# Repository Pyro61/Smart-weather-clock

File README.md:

# Smart Weather Clock

A real-time clock system with configurable alarms and integrated weather sensing, built on the STM32G474RE microcontroller. Combines internal and external sensors with a simple user interface and Bluetooth-based data expansion.

---

## Project Goals

This project was developed as a learning exercise with the following goals:

- Practice **bare-metal programming** using direct register access on STM32 microcontrollers
- Design the system so that most tasks are handled via **interrupts**, not the main loop — to reduce power consumption
- Learn to build embedded projects using a **build system (CMake)** instead of IDE-generated Makefiles
- Improve fluency with **Git version control** and good repository structure
- Gain experience in **PCB design**

---

## Features

- Real-Time Clock (RTC) with support for a single configurable alarm
- Weather sensing:
  - **Internal sensors**:
    - Temperature & Pressure: LPS25HB (I2C)
    - Humidity: SHT20 (I2C)
  - **External sensors** (via Bluetooth HC-05):
    - Temperature, Pressure, Humidity, Rain Detection
- Periodic weather update every 10 seconds
- Automatic low-power sleep mode:
  - System enters sleep after completing all tasks in the main loop
  - Wakes up on interrupts (e.g., timer or button press)
- User-selectable weather data source (internal or external)
- Alarm notifications:
  - Display alert
  - External buzzer module with built-in sound generator (controlled via GPIO)
- LCD display: 20x4 alphanumeric, driven by HD44780 controller
- User interface:
  - Push-buttons for navigation and settings
  - Potentiometer for adjusting LCD contrast

---

## Hardware Overview

- **Microcontroller**: STM32G474RE
- **Display**: 20x4 LCD with HD44780 controller (parallel interface)
- **Internal Sensors**:
  - LPS25HB (temperature and pressure, I2C)
  - SHT20 (humidity, I2C)
- **External Sensor Module**:
  - Communicates over UART via HC-05 Bluetooth
  - Sends temperature, pressure, humidity, and rain data
- **Buzzer Module**:
  - External buzzer with internal sound generator
  - Controlled via logic-level GPIO
- **User Inputs**:
  - Buttons:
    - OK / Mode
    - Up
    - Down
    - Left
    - Right
  - Potentiometer for LCD contrast

---

## How It Works

1. On startup, the system initializes:
   - MCU embedded peripherals (RTC, UART, GPIO, RTC etc.)
   - Internal sensors
   - LCD

3. Default behavior after power reset:
   - RTC time = 00:00:00
   - Alarm = disabled
   - Weather readings from internal sensors

4. System behavior:
   - Sensor readings are updated every 10 seconds
   - Every second current time and sensor readings are displayed on the screen
   - After processing all events and interrupts, the system enters low-power mode until the next interrupt

5. The default screen shows:
   - Current time
   - Alarm status
   - Sensor data (internal by default)

6. Pressing **OK / Mode** opens a menu with 4 options. The currently selected option is marked with `>` e.g:
```
   > 1. weather indoor  
     2. weather outdoor  
     3. set time  
     4. set alarm
```

7. Navigation:
   - **Up / Down** to move through options
   - **OK / Mode** to select
   - In `Set Time` and `Set Alarm`:
     - **Left / Right** to move between HH:MM:SS
     - **Up / Down** to adjust values

8. Alarm behavior:
   - When alarm is enabled and the current time matches the alarm:
     - "ALARM" screen is displayed
     - Buzzer is activated via GPIO

---

## User Interface

After system startup and peripheral initialization, the main screen displays:
- Current time (reset to 00:00:00 after power-off — no backup battery for RTC)
- Alarm status (disabled after power reset)
- Live weather readings from internal sensors

### Navigation Summary

- **OK / Mode**: Enter menu / confirm selection
- **Up / Down**: Scroll through menu or increment/decrement values
- **Left / Right**: Switch between hours, minutes, seconds

---

## Getting Started

1. Clone this repository.
2. Build the project using CMake
3. Flash the firmware to STM32G474RE (e.g., Nucleo board).
4. Connect all sensors and peripherals according to the labeled connectors on the [custom PCB](pcb/main_board/main_board_pcb.png) or according to [wiring diagram](pcb/main_board/main_board_schematic.png).

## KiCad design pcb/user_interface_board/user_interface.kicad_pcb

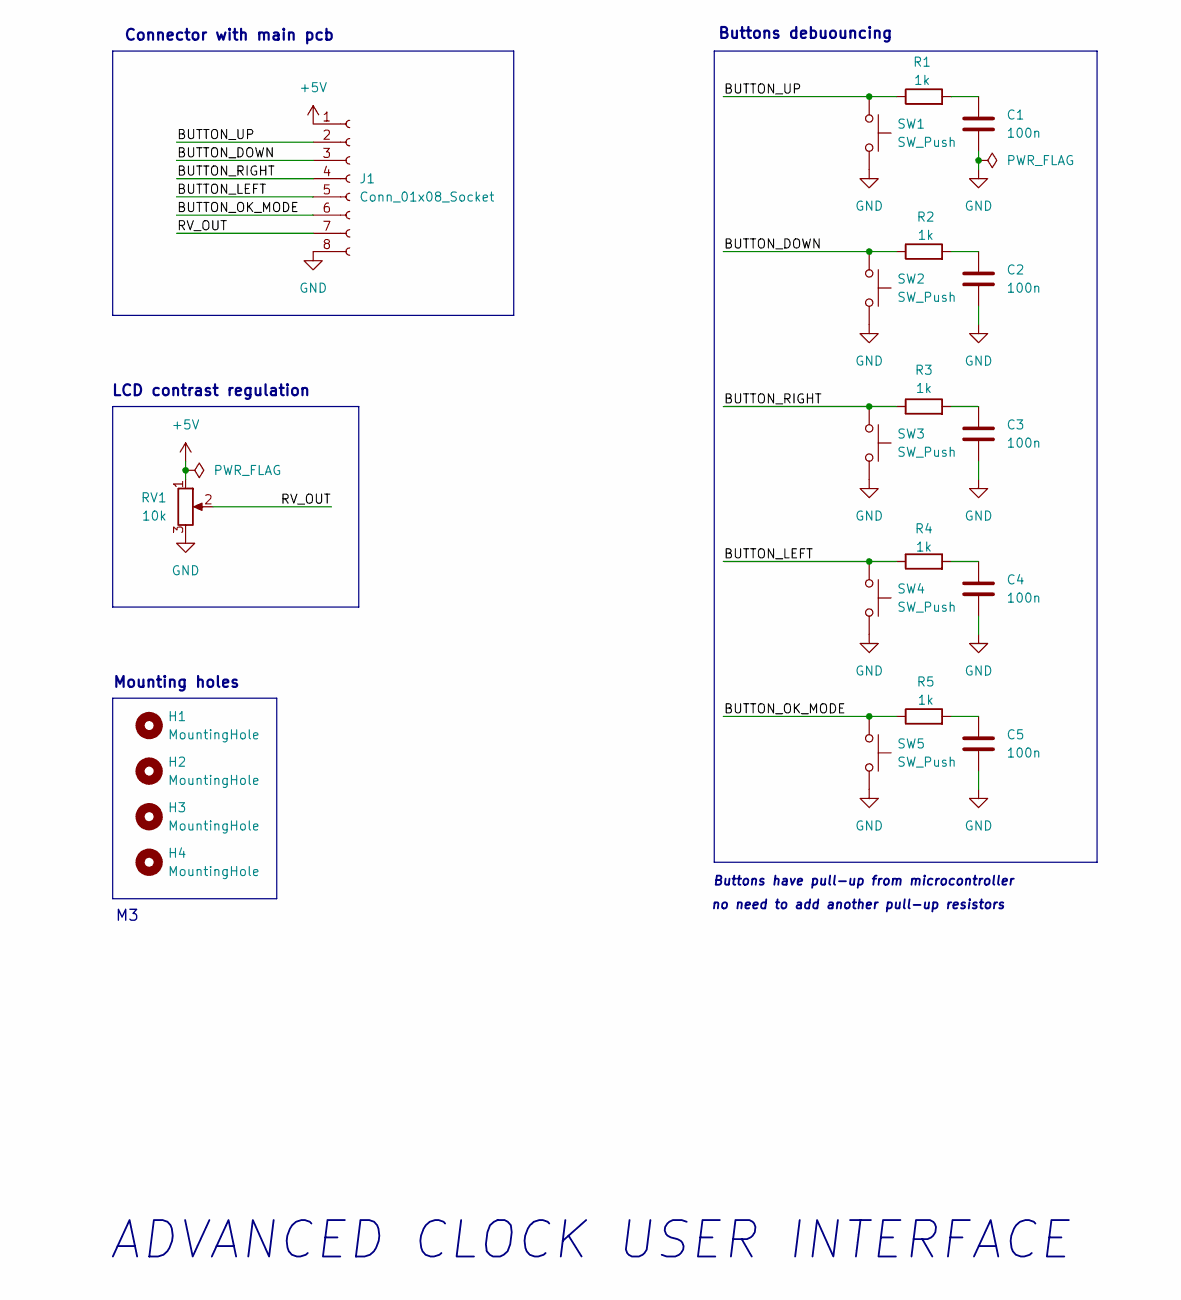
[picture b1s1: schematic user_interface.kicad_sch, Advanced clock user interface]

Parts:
C1, C2, C3, C4, C5: 100n; C_0402_1005Metric
H1, H2, H3, H4: MountingHole; MountingHole_3.2mm_M3
J1: Conn_01x08_Socket; PinSocket_1x08_P2.54mm_Vertical
R1, R2, R3, R4, R5: 1k; R_0402_1005Metric
RV1: 10k; Potentiometer_Bourns_3339P_Vertical_HandSoldering
SW1, SW2, SW3, SW4, SW5: SW_Push; SW_PUSH_6mm_H7.3mm

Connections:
+5V: J1.1, RV1.1
/BUTTON_DOWN: J1.3, R2.1, SW2.1
/BUTTON_LEFT: J1.5, R4.1, SW4.1
/BUTTON_OK_MODE: J1.6, R5.1, SW5.1
/BUTTON_RIGHT: J1.4, R3.1, SW3.1
/BUTTON_UP: J1.2, R1.1, SW1.1
/RV_OUT: J1.7, RV1.2
GND: C1.2, C2.2, C3.2, C4.2, C5.2, J1.8, RV1.3, SW1.2, SW2.2, SW3.2, SW4.2, SW5.2
unnamed: C1.1, R1.2
unnamed: C2.1, R2.2
unnamed: C3.1, R3.2
unnamed: C4.1, R4.2
unnamed: C5.1, R5.2

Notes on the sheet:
Buttons have pull-up from microcontroller
Mounting holes
LCD contrast regulation
Buttons debuouncing
no need to add another pull-up resistors
Connector with main pcb
ADVANCED CLOCK USER INTERFACE

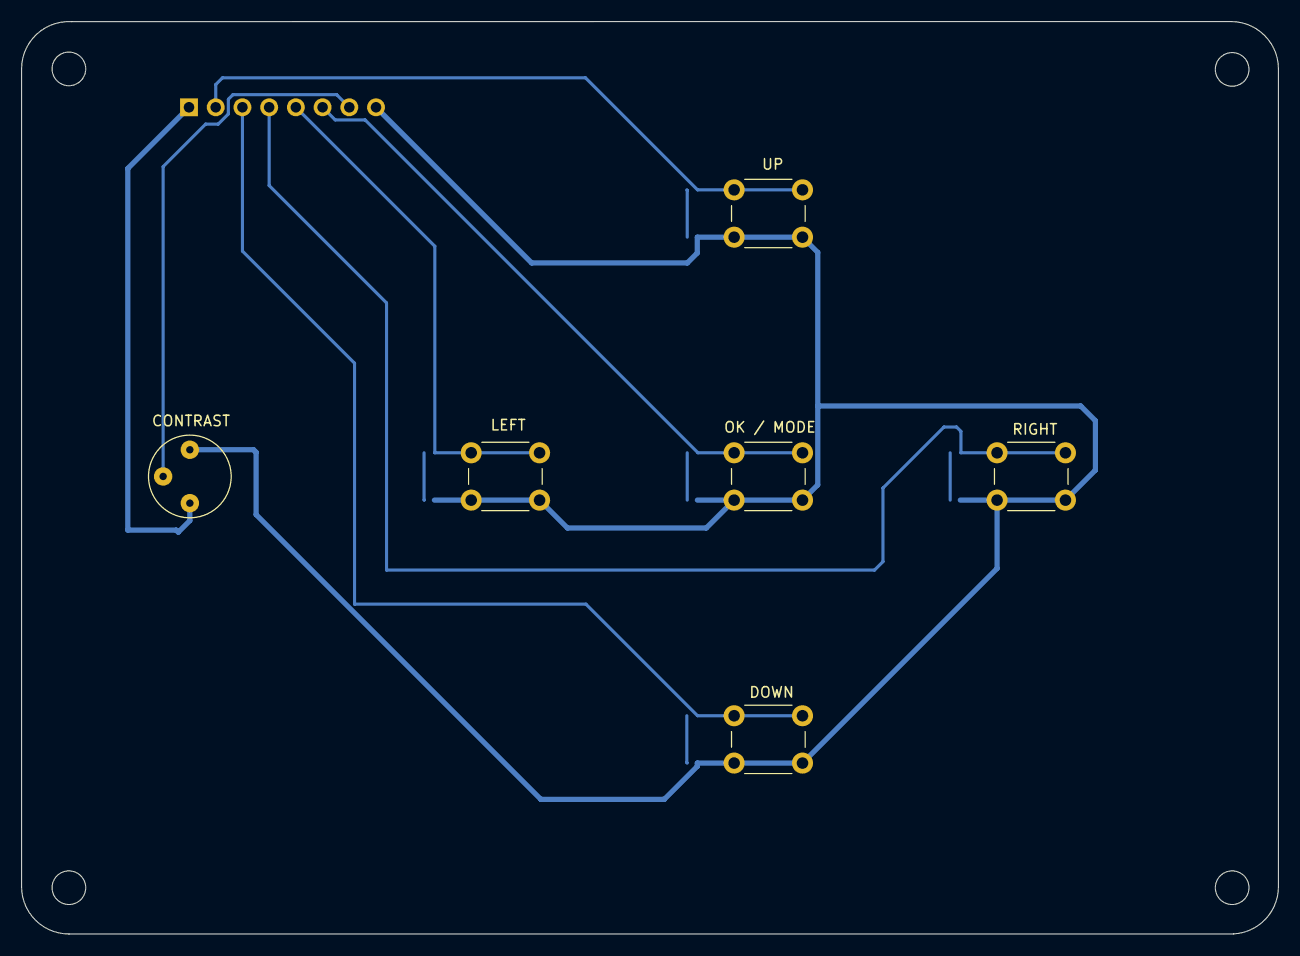
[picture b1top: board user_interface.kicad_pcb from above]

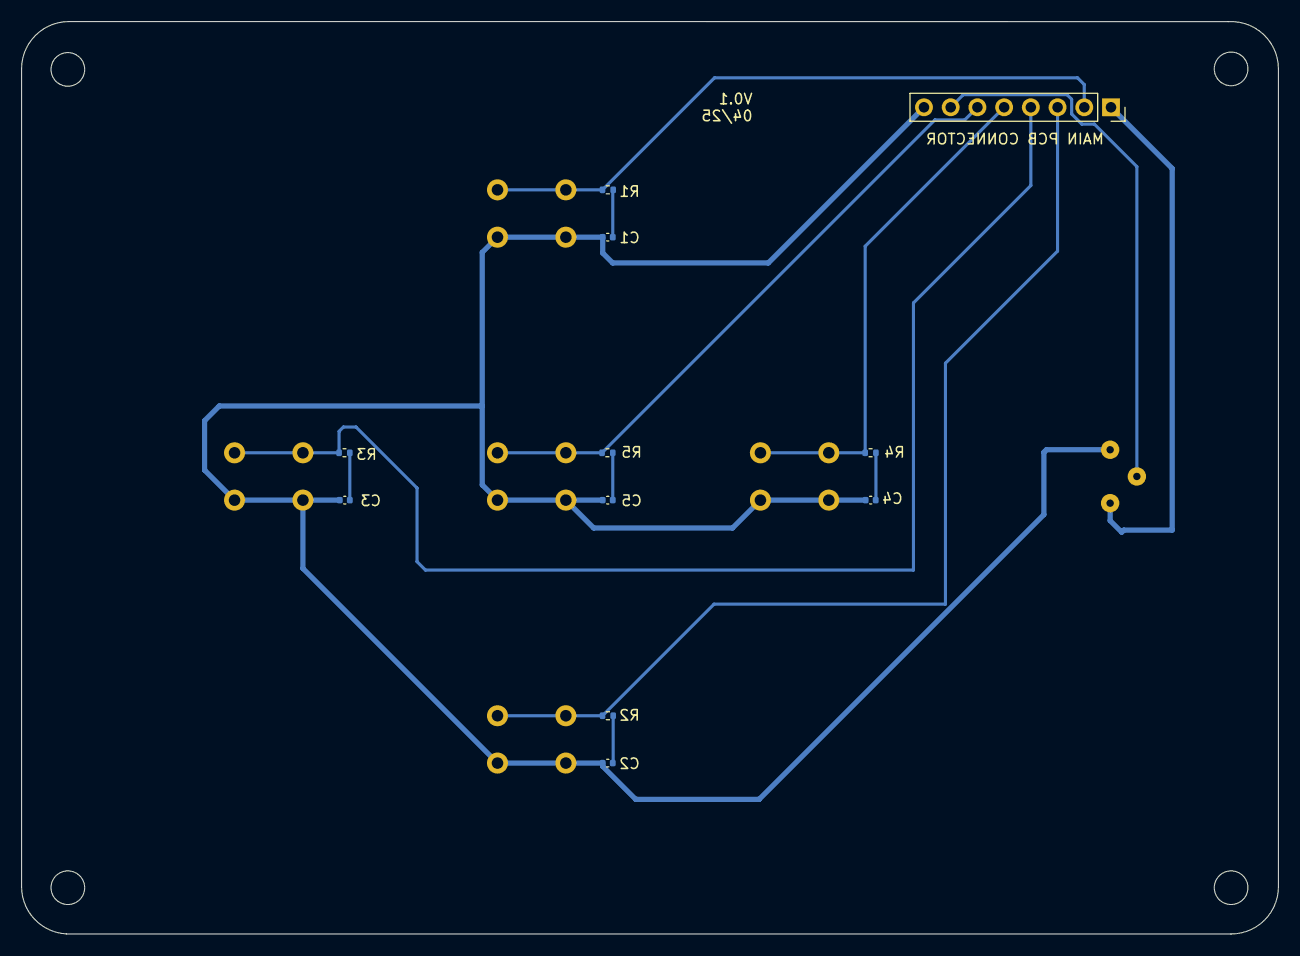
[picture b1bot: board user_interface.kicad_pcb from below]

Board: 2 copper layers, 119.5 x 86.8 mm, 21 parts (11 on the bottom side), 13 nets.

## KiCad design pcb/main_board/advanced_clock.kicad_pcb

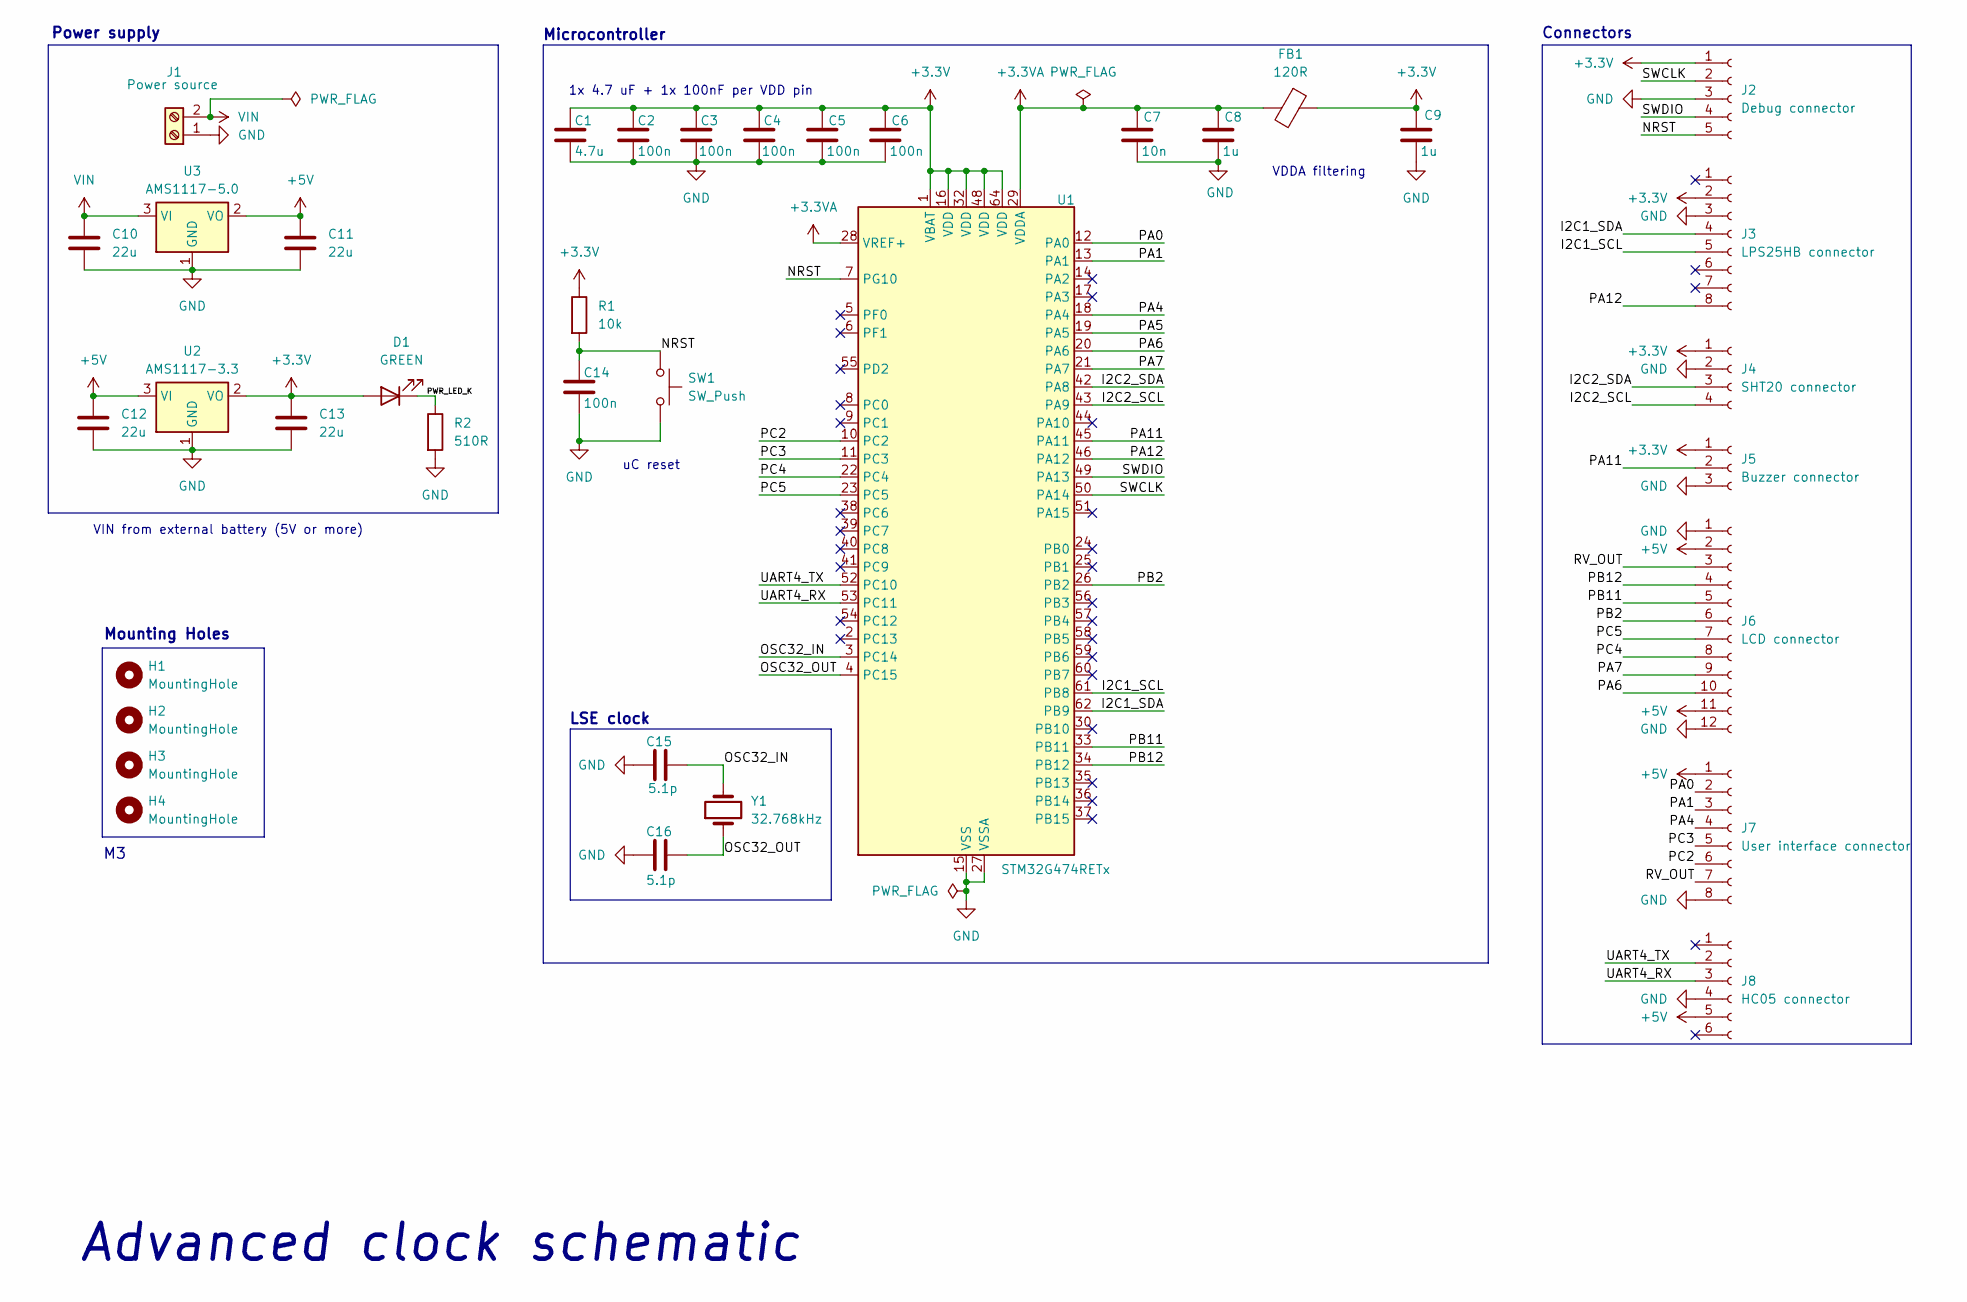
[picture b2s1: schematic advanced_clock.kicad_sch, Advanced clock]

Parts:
C1: 4.7u; C_0504_1310Metric
C2, C3, C4, C5, C6, C14: 100n; C_0402_1005Metric
C7: 10n; C_0402_1005Metric
C8, C9: 1u; C_0402_1005Metric
C10, C11, C12, C13: 22u; C_0805_2012Metric
C15, C16: 5.1p; C_0402_1005Metric
D1: GREEN; LED_0402_1005Metric
FB1: 120R; L_0603_1608Metric
H1, H2, H3, H4: MountingHole; MountingHole_3.2mm_M3
J1: Power source; TerminalBlock_Phoenix_MKDS-1,5-2-5.08_1x02_P5.08mm_Horizont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
J2: Debug connector; PinSocket_1x05_P2.54mm_Vertical
J3: LPS25HB connector; PinSocket_1x08_P2.54mm_Vertical
J4: SHT20 connector; PinSocket_1x04_P2.54mm_Vertical
J5: Buzzer connector; PinSocket_1x03_P2.54mm_Vertical
J6: LCD connector; PinSocket_1x12_P2.54mm_Vertical
J7: User interface connector; PinSocket_1x08_P2.54mm_Vertical
J8: HC05 connector; PinSocket_1x06_P2.54mm_Vertical
R1: 10k; R_0402_1005Metric
R2: 510R; R_0402_1005Metric
SW1: SW_Push; SW_PUSH_6mm_H7.3mm
U1: STM32G474RETx; LQFP-64_10x10mm_P0.5mm
U2: AMS1117-3.3; SOT-223-3_TabPin2
U3: AMS1117-5.0; SOT-223-3_TabPin2
Y1: 32.768kHz; Crystal_SMD_2012-2Pin_2.0x1.2mm

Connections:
+3.3V: C1.1, C2.1, C3.1, C4.1, C5.1, C6.1, C9.1, C13.1, D1.2 (A), FB1.1, J2.1, J3.2, J4.1, J5.1, R1.1, U1.1 (VBAT), U1.16 (VDD), U1.32 (VDD), U1.48 (VDD), U1.64 (VDD), U2.2 (VO)
+3.3VA: C7.1, C8.1, FB1.2, U1.28 (VREF+), U1.29 (VDDA)
+5V: C11.1, C12.1, J6.2, J6.11, J7.1, J8.5, U2.3 (VI), U3.2 (VO)
/I2C1_SCL: J3.5, U1.61 (PB8)
/I2C1_SDA: J3.4, U1.62 (PB9)
/I2C2_SCL: J4.4, U1.43 (PA9)
/I2C2_SDA: J4.3, U1.42 (PA8)
/NRST: C14.1, J2.5, R1.2, SW1.1, U1.7 (PG10)
/OSC32_IN: C15.2, U1.3 (PC14), Y1.2
/OSC32_OUT: C16.2, U1.4 (PC15), Y1.1
/PA0: J7.2, U1.12 (PA0)
/PA1: J7.3, U1.13 (PA1)
/PA4: J7.4, U1.18 (PA4)
/PA5: U1.19 (PA5)
/PA6: J6.10, U1.20 (PA6)
/PA7: J6.9, U1.21 (PA7)
/PA11: J5.2, U1.45 (PA11)
/PA12: J3.8, U1.46 (PA12)
/PB2: J6.6, U1.26 (PB2)
/PB11: J6.5, U1.33 (PB11)
/PB12: J6.4, U1.34 (PB12)
/PC2: J7.6, U1.10 (PC2)
/PC3: J7.5, U1.11 (PC3)
/PC4: J6.8, U1.22 (PC4)
/PC5: J6.7, U1.23 (PC5)
/PWR_LED_K: D1.1 (K), R2.1
/RV_OUT: J6.3, J7.7
/SWCLK: J2.2, U1.50 (PA14)
/SWDIO: J2.4, U1.49 (PA13)
/UART4_RX: J8.3, U1.53 (PC11)
/UART4_TX: J8.2, U1.52 (PC10)
GND: C1.2, C2.2, C3.2, C4.2, C5.2, C6.2, C7.2, C8.2, C9.2, C10.2, C11.2, C12.2, C13.2, C14.2, C15.1, C16.1, J1.1, J2.3, J3.3, J4.2, J5.3, J6.1, J6.12, J7.8, J8.4, R2.2, SW1.2, U1.15 (VSS), U1.27 (VSSA), U1.31 (VSS), U1.47 (VSS), U1.63 (VSS), U2.1 (GND), U3.1 (GND)
VIN: C10.1, J1.2, U3.3 (VI)

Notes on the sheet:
1x 4.7 uF + 1x 100nF per VDD pin
Mounting Holes
uC reset
Power supply
VDDA filtering
VIN from external battery (5V or more)
LSE clock
Connectors
Microcontroller
Advanced clock schematic

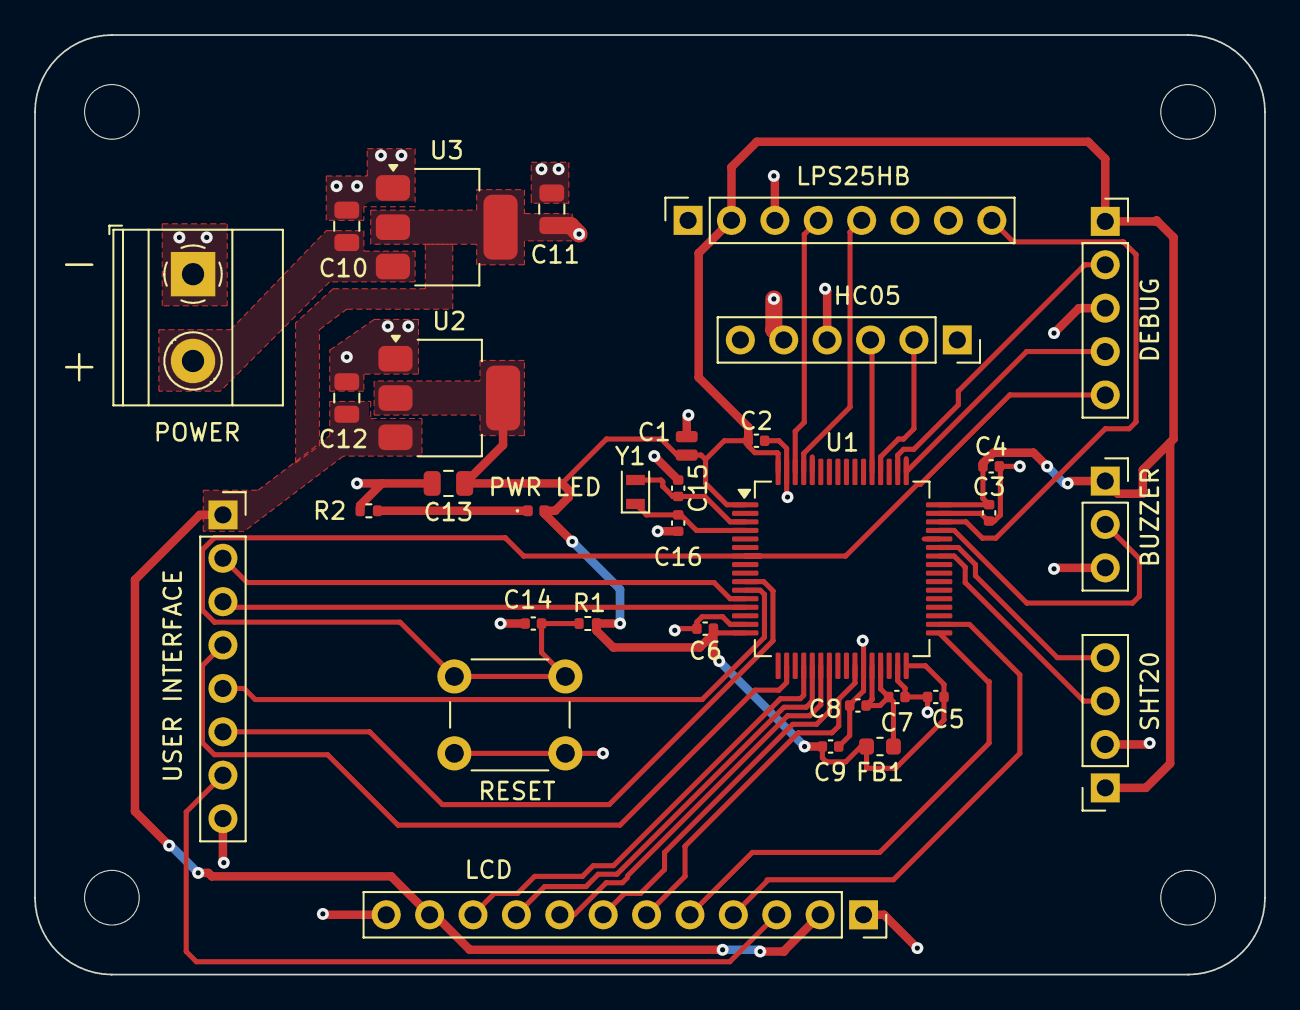
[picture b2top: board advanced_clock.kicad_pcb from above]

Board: 2 copper layers, 72.0 x 55.0 mm, 37 parts (0 on the bottom side), 32 nets.

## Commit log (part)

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2024-12-31 project: add .gitignore
2024-12-31 project: add cube generated files
2024-12-31 project: add main CMakeLists.txt file
2024-12-31 test: add unity framework files
2024-12-31 project: add svd file
2024-12-31 project: update .gitignore
2024-12-31 project: add toolchain and flags files
2024-12-31 test: add template test files
2024-12-31 src: add events module files
2024-12-31 src: add safe state module files
2024-12-31 src: add sys_comm module files
2024-12-31 src: add weather sensors module files
2024-12-31 src: add types header file
2024-12-31 src: add logic init module files
2024-12-31 test: add events module unit tests files
2024-12-31 test: add system communication unit tests files
2024-12-31 project: update main CMakeLists.txt file
2025-01-01 src: change core hw submodule name to mcu_hw
2025-01-01 core_clock: create source files
2025-01-01 src: add mcu_hw_init.c to compilation
2025-01-01 fpu: add implementation
2025-01-01 fpu: create source files
2025-01-01 mcu_hw_init: add fpu_init
2025-01-01 src: add fpu.c to compilation
2025-01-01 main: add mcu_hw_init to main
2025-01-01 mcu_hw_init: add source files
2025-01-01 main: remove uninitialised fpu warning
2025-01-01 LPS25HB: create source files
2025-01-01 gpio: create source files
2025-01-01 LPS25HB: add header file with register defines
2025-01-08 drivers: add missing stdint include
2025-01-08 src: add gpio.c to compilation
2025-01-08 control: add app control module files
2025-01-08 spi: add init function implementation
2025-01-08 spi: create source files
2025-01-08 src: add spi.c to compilation
2025-01-11 spi: add write polling function implementation
2025-01-11 spi: write dma recv function implementation
2025-01-11 spi: change multiple requests handling mechanism
    So far it was checking bus state bit is spi status register, now it's variable indicating currect spi state. Higher logic modules than want to use spi, must first check if is spi bus free, then use w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
2025-01-19 gpio: add exti configuration
2025-01-19 mcu_hw: add spi_init to mcu_hw_init
2025-01-19 gpio: fix set af fun
    It wasn't writing af for pins 8 and above
2025-01-19 i2c: add implementation
    init, write/read polling, read dma
2025-01-19 mcu_hw: add tim inits to mcu_hw_init
2025-01-19 LPS25HB: change reg addresses from defines to enum, highlight default registers values
2025-01-19 LPS25HB: add implementation
2025-01-19 mcu_hw: add i2c1_init to init
2025-01-19 aht15: create files
2025-01-19 i2c: separate i2c1 and i2c2 code spaces
2025-02-02 i2c: add i2c2 implementation
2025-02-02 aht15: add implementation
    -init
    -measuring trigger
    -get humidity
    -get temperature
2025-02-02 tim: add time measurement non-blocking implementation
2025-02-02 aht15: change implementation
    calls tim_meas_no_block with 80ms measurement inside aht15_trigger_measurement fun, after that time data is read from sensor
2025-02-03 uart: add implementation of uart4
2025-02-03 HC05: add implementation
2025-02-08 events: add buttons pressed, refresh and alarm event names
2025-02-08 events: increase max events to 25
2025-02-08 display: add display interface
2025-02-08 unit_test: fix test fail is events module
    create more mock functions to pass ReachMaxSubscribersThenSubscribe1MoreEventAndCallEvent test
2025-02-09 unit test: main_state_machine: add display mock functions
2025-02-09 unit test: main_state_machine: mode selection: add OnEntryDisplayOutput test
2025-02-09 unit test: add unit test configuration for main state machine
    every state will be tested in separation, no tests for all state machine
2025-02-09 unit test: main_state_machine: mode selection: add WhenSelectedModeIs1ClickUpButtonThenSelectedModeIsStill1 test
2025-02-09 unit test: main_state_machine: mode selection: add OnExitDisplayOutput test
2025-02-09 unit test: main_state_machine: mode selection: refactoring test code
2025-02-09 unit test: main_state_machine: mode selection: add AfterEntrySelectedModeIs1 test
2025-02-09 unit test: main_state_machine: mode selection: add WhenSelectedModeIs1ClickDownButtonThenSelectedModeIs2 test
2025-02-09 unit test: main_state_machine: mode selection: add WhenSelectedModeIs2ClickDownButtonThenSelectedModeIs3 test
2025-02-09 state_mode_selecttion: fix failing test
    add missing reset of selected_mode in state entry
2025-02-09 unit test: main_state_machine: mode selection: add WhenSelectedModeIs3ClickDownButtonThenSelectedModeIs4 test
2025-02-09 unit test: main_state_machine: mode selection: add WhenSelectedModeIs1ClickDownButtonAfterUpButtonThenSelectedModeIsStill1 test
2025-02-09 unit test: main_state_machine: mode selection: add SelectedMode1MessageAfterRefreshDontHaveSelectedModeSign test
2025-02-09 unit test: main_state_machine: mode selection: add AfterDoubleRefreshThereIsSelectedSign test
2025-02-09 unit test: main_state_machine: mode selection: add AfterRefreshChangedSelectedModeThenThereIsSelectedModeSign test
2025-02-09 unit test: main_state_machine: mode selection: add AfterRefreshChangedSelectedModeAfterThatRefreshThenThereIsNoSelectedSign test
2025-02-09 main state machine: add handling last state in state entry
2025-02-09 state mode selection: handle last state in entry function
2025-02-13 types: add time struct definition
2025-02-13 alarm: add function prototypes
    needed in handling weather in/out states
2025-02-13 adapter sys comm: add copying recv buffer to given buffer function
2025-02-13 events: add 1s elapsed event and change send event id
2025-02-13 state weather out: add implemetation
2025-02-14 weather measurement state machine: delete module
2025-02-15 main state machine: change state switching logic
    bypassing mode selection when switching modes, so for example after when exiting weather in mode to set alarm via mode selection come back directly to weather in bypassing mode selection
2025-02-15 state set time: add implementation
2025-02-15 unit test: add time mock functions
2025-02-15 state set time: fix compilation error
    used wrong enum
2025-02-15 unit test: fix compilation error
    not used static in test buffer definition in mode_selection_test.c
2025-02-15 set time unit test: add OnEntryDisplayOutput test
2025-02-15 set time unit test: add OnExitDisplayOutput test
2025-02-15 set time unit test: add WhenEditingHourTensPressLeftButtonAfterThatRefreshThenEditingTimeIsStillHourTens test
2025-02-15 state set time: fix failing test
    Reading next position from set_time_parts_buf_position array instead of current
2025-02-15 set time unit test: add WhenEditingHourTensPressRightButtonAfterThatRefreshThenEditingTimeIsHourUnits test
2025-02-16 set time unit test: add WhenEditingSecondTensPressLeftButtonAfterThatRefreshThenEditingTimeIsMinuteUnits test
2025-02-16 set time unit test: add WhenEditingSecondUnitsPressRightButtonAfterThatRefreshThenEditingTimeIsStillSecondUnits test
2025-02-16 set time unit test: add WhenEditingHourTensPressDownButtonThenHourTensIsStill0 test
2025-02-16 dtate set time: fix implementation
    prepare buf was editing wrong positions of the buffer and was writing values directly casted from int to char instead of value + '0'
2025-02-16 state set time: refactoring
    in prepare_buf use given time value instead of tmp values read from get_time_part_value
2025-02-16 set time unit test: add WhenEditingHourTensPressUpButtonThenHourTensIs1 test
2025-02-16 state set time: fix implementation
    Change modulo 2 result from 1 to 0 in checking if edited time part in tens or units
    Additionally change unit add/subtract value from 0 to 1
2025-02-16 set time unit test: add WhenEditingHourTensPressUpButton3TimesThenHourTensIs2InsteadOf3 test
2025-02-16 set time unit test: add WhenEditingHourUnitsPressUpButton10TimesThenHourIs9InsteadOf10 test
2025-02-16 set time unit test: add WhenTimeIsSetTo00_50_00AndEditingPartIsMinuteUnitsPressDownButtonTimeDoNotChange test
2025-02-16 set time unit test: add WhenTimeIsSetTo23_00_00AndEditingPartIsHourUnitsPressUpButtonThenTimeDoNotChange test
2025-02-16 set time unit test: add set_time, WhenTimeIsSetTo00_00_19AndEditingPartIsSecondUnitsRefresh4TimesAndTimeIsTheSame test
2025-02-16 set time unit test: add WhenEditingHourTensPressRightButton2TimesAfterThatLeftButton1TimeThenEditingTimeIsHourUnits test
2025-02-16 set time unit test: add reading display buffer in press left/right button
2025-02-16 state set time: fix implementation
    Add preparing buffer and printing display in right/left button state reactions
2025-02-16 set time unit test: add WhenTimeIsSetTo01_00_00RefreshAfterThatPressDownButtonThenDisplayShows00_00_00 test
2025-02-16 state set time: change display window output message
    Add SET TIME at beginning
2025-02-16 state set alarm: add implementation
2025-02-16 set alarm unit test: add alarm mock functions
2025-02-16 set alarm unit test: add tests
    Tests are the same as set time tests
2025-02-16 alarm: add alarm start and stpp function declarations
2025-02-16 alarm unit test: add alarm and time mock function implementations
2025-02-16 alarm unit test: configure tests
2025-02-20 alarm unit test: add OnEntryDisplayOutput test
2025-02-20 state alarm: fix failing test
    change time part buffer position defines
2025-02-20 alarm unit test: add PressedOkButtonReturnedStateIsTheSameAsGivenToStateEntrytest
2025-02-20 alarm unit test: add WriteTimeThenEntryAlarmStateTimeShownOnDisplayIsTheSameAsWritten test
2025-02-21 alarm unit test: add AfterRefreshAlarmStringIsGone test
2025-02-22 state alarm: fix failing test
    add reseting time in test setup
    change alarm blink buffer positions
2025-02-22 alarm unit test: refactoring
    delete unnecessary functions
    add entry message define
2025-02-22 main state machine: add unsaved changes
2025-02-22 main state machine: fix implementation
    mode selection: add static to display functions holder
    weather in/out: change logic or to logic and in checking if time is correct
2025-02-22 events: remove refresh event
2025-02-22 time: add implementation
2025-02-22 alarm: add implementation
2025-02-22 Src: add time.c to compilation
2025-02-23 rtc: add implementation
2025-02-23 alarm: remove alarm start/stop from alarm interface
2025-02-23 time: add const modifier to passing arguments
2025-02-24 buzzer: add implementation
2025-03-05 HD44780: add checking busy flag implementation
    Still blocking implementation, all functions using it must be called from main loop
2025-03-06 gpio: add handling EXTI from other ports than A
2025-03-06 LPS25HB: add port to EXTI config
2025-03-06 buttons: add implementation
2025-03-09 adapter sys comm: change copy data from buf fun prototype name
2025-03-09 events: change event end id to event send value
2025-03-09 alarm: add alarm start/stop functions implementation
2025-03-09 state machine: add state functions to states array, add const to display interface in init
2025-03-09 rtc: fix wakeup timer irq not called bug
2025-03-09 HD44780: fix writing not always from position 0,0 bug
2025-03-09 logic init: add implementation
2025-03-09 main: add production code
2025-03-10 rtc: change irqs priority
2025-03-10 tim: change delay tim irq priority
2025-03-10 lps25hb: subscribe measure fun to EVENT_MEAS_DELAY_ELAPSED
2025-03-10 i2c: change irqs priority
2025-03-10 state set time: add const to display funs holder
2025-03-10 state alarm: add const to display funs holder
2025-03-10 state mode selection: add const to display funs holder
2025-03-10 HD44780: add handling writing full line and then \n sign
    before there was adding 2 new lines
2025-03-18 aht15: add event subscribe to init
2025-03-18 sht20: add implementation
    replace aht15 with sht20 because aht15stopped working
2025-03-18 i2c: add dmamux clock enable in i2c init functions, change order of writing i2c2 registers in write polling
2025-03-18 uart: change dma channgel using in uart4
2025-03-18 project: change measurement delay from 30s to 10s
2025-05-01 iwdg: add implementation
2025-05-01 low power: add implementation
2025-05-01 exceptions: add implementation
2025-05-01 HD44780: change pins due to pcb desing
2025-05-02 datasheets: add mcu and external devices datasheets
2025-05-02 pcb: add kicad files and pcb/schematic screens
